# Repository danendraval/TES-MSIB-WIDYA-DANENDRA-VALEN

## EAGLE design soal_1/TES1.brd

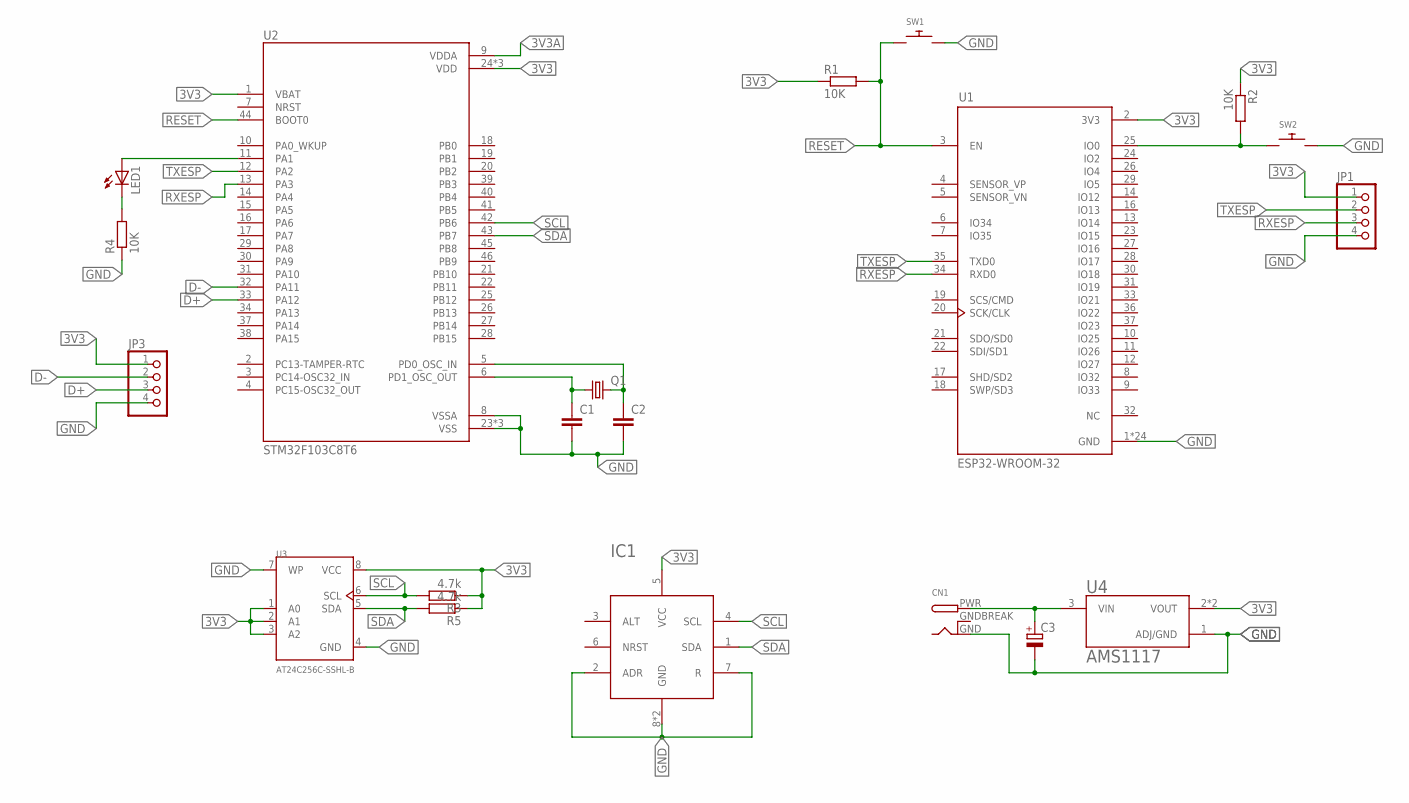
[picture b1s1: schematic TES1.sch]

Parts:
C1, C2: C-EUC0805; C0805
C3: CPOL-EU150CLZ-0810; 150CLZ-0810
CN1: DCBARRELPTH; DCJACK_2MM_PTH
IC1: SHT31; SON50P250X250X90-9T110X180N
JP1, JP3: PINHD-1X4; 1X04
LED1: LEDCHIP-LED0805; CHIP-LED0805
Q1: CRYSTALHC49U-V; HC49U-V
R1, R2, R4: 10K; R0805
R3, R5: 4.7k; R0805
SW1, SW2: SWITCH_PUSHBUTTONC&K_KSS; BTN_CK_KSS
U1: ESP32-WROOM-32; MODULE_ESP32-WROOM-32
U2: STM32F103C8T6; QFP50P900X900X160-48N
U3: AT24C256C-SSHL-B; SOIC127P600X175-8N
U4: AMS1117; SOT229P700X180-4N

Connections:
3V3: IC1.5 (VCC), JP1.1, JP3.1, R1.1, R2.1, R3.1, R5.1, U1.2 (3V3), U2.1 (VBAT), U2.24 (VDD), U2.36 (VDD), U2.48 (VDD), U3.1 (A0), U3.2 (A1), U3.3 (A2), U3.8 (VCC), U4.2 (VOUT), U4.4 (VOUT)
3V3A: U2.9 (VDDA)
12V: C3.+, CN1.PWR, U4.3 (VIN)
D+: JP3.3, U2.33 (PA12)
D-: JP3.2, U2.32 (PA11)
GND: C1.2, C2.2, C3.-, CN1.GND, IC1.2 (ADR), IC1.7 (R), IC1.8 (GND), IC1.9 (GND), JP1.4, JP3.4, R4.1, SW1.P$2, SW2.P$2, U1.1 (GND), U1.15 (GND), U1.38 (GND), U1.39_1 (GND), U1.39_2 (GND), U1.39_3 (GND), U1.39_4 (GND), U1.39_5 (GND), U1.39_6 (GND), U1.39_7 (GND), U1.39_8 (GND), U1.39_9 (GND), U1.39_10 (GND), U1.39_11 (GND), U1.39_12 (GND), U1.39_13 (GND), U1.39_14 (GND), U1.39_15 (GND), U1.39_16 (GND), U1.39_17 (GND), U1.39_18 (GND), U1.39_19 (GND), U1.39_20 (GND), U1.39_21 (GND), U2.8 (VSSA), U2.23 (VSS), U2.35 (VSS), U2.47 (VSS), U3.4 (GND), U3.7 (WP), U4.1 (ADJ/GND)
GNDBREAK: CN1.GNDBREAK
unnamed: C1.1, Q1.1, U2.6 (PD1_OSC_OUT)
unnamed: C2.1, Q1.2, U2.5 (PD0_OSC_IN)
unnamed: R2.2, SW2.P$1, U1.25 (IO0)
unnamed: LED1.C, R4.2
unnamed: LED1.A, U2.11 (PA1)
RESET: R1.2, SW1.P$1, U1.3 (EN), U2.44 (BOOT0)
RXESP: JP1.3, U1.34 (RXD0), U2.13 (PA3)
SCL: IC1.4 (SCL), R3.2, U2.42 (PB6), U3.6 (SCL)
SDA: IC1.1 (SDA), R5.2, U2.43 (PB7), U3.5 (SDA)
TXESP: JP1.2, U1.35 (TXD0), U2.12 (PA2)

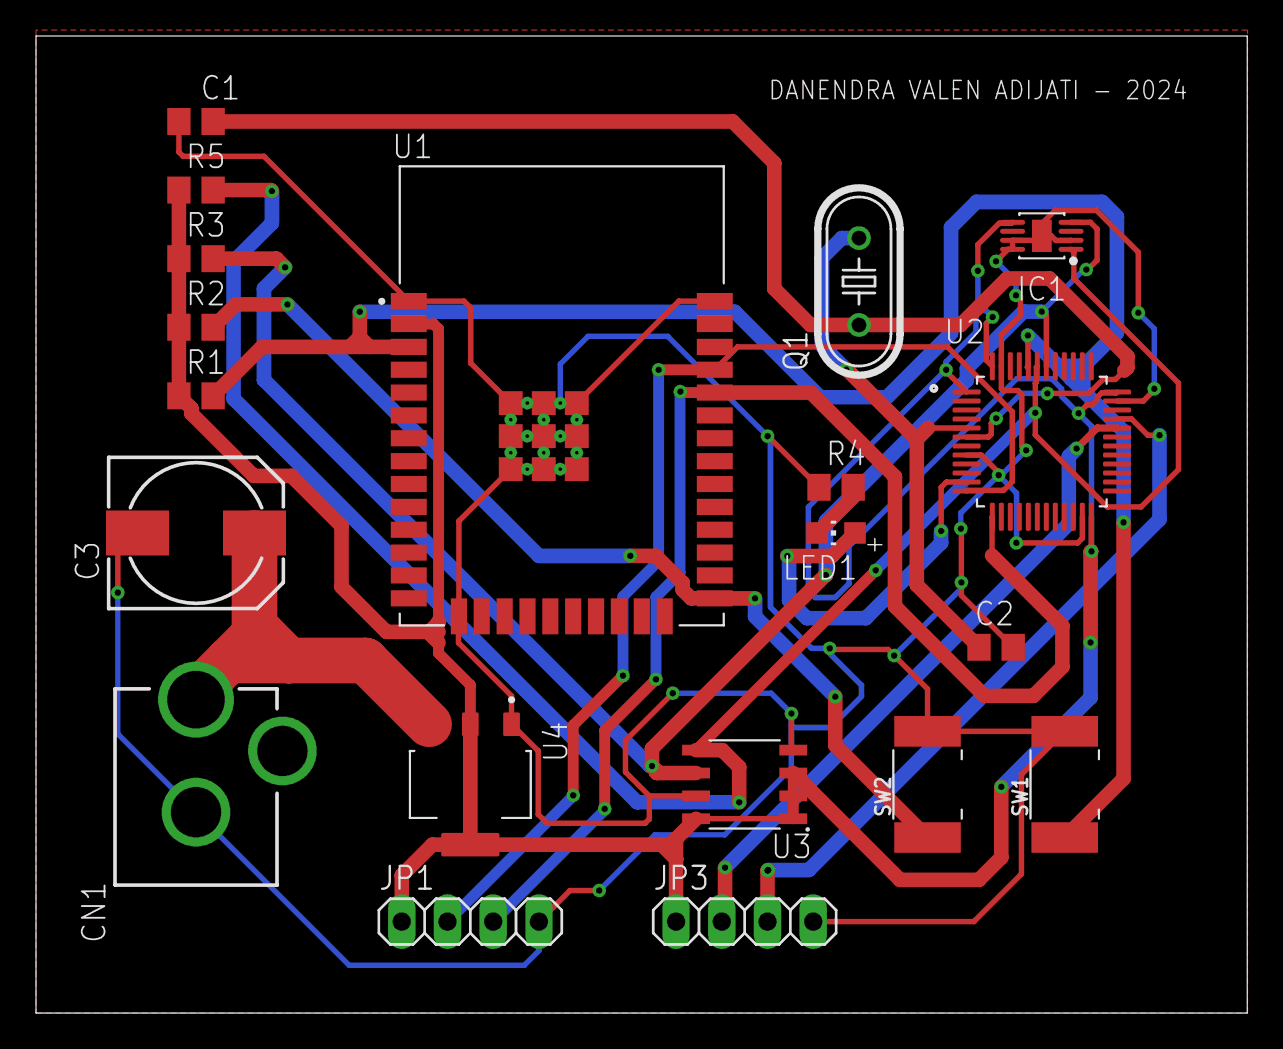
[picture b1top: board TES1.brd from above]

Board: 2 copper layers, 67.3 x 54.3 mm, 20 parts (0 on the bottom side), 15 nets.

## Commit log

2024-08-28 arduino.ino
